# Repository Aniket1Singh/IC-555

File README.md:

# IC-555
PCB design of IC-555 timer working in Astable Mode.

This repository contains the design files for a PCB based on the IC-555 timer in astable mode. The design was created using KiCad, and all the necessary files are included here.

What’s Included

KiCad project files

Gerber files for PCB fabrication

Schematic and board design

How to Use

Open the KiCad project files to view or modify the design.

Use the Gerber files to manufacture the PCB.

Assemble the circuit by soldering the required components.

Applications-
LED blinking circuits,
Square wave generators,
Simple tone generators,
Learning about the IC-555 timer.
Feel free to use or modify this design for your projects! 😊

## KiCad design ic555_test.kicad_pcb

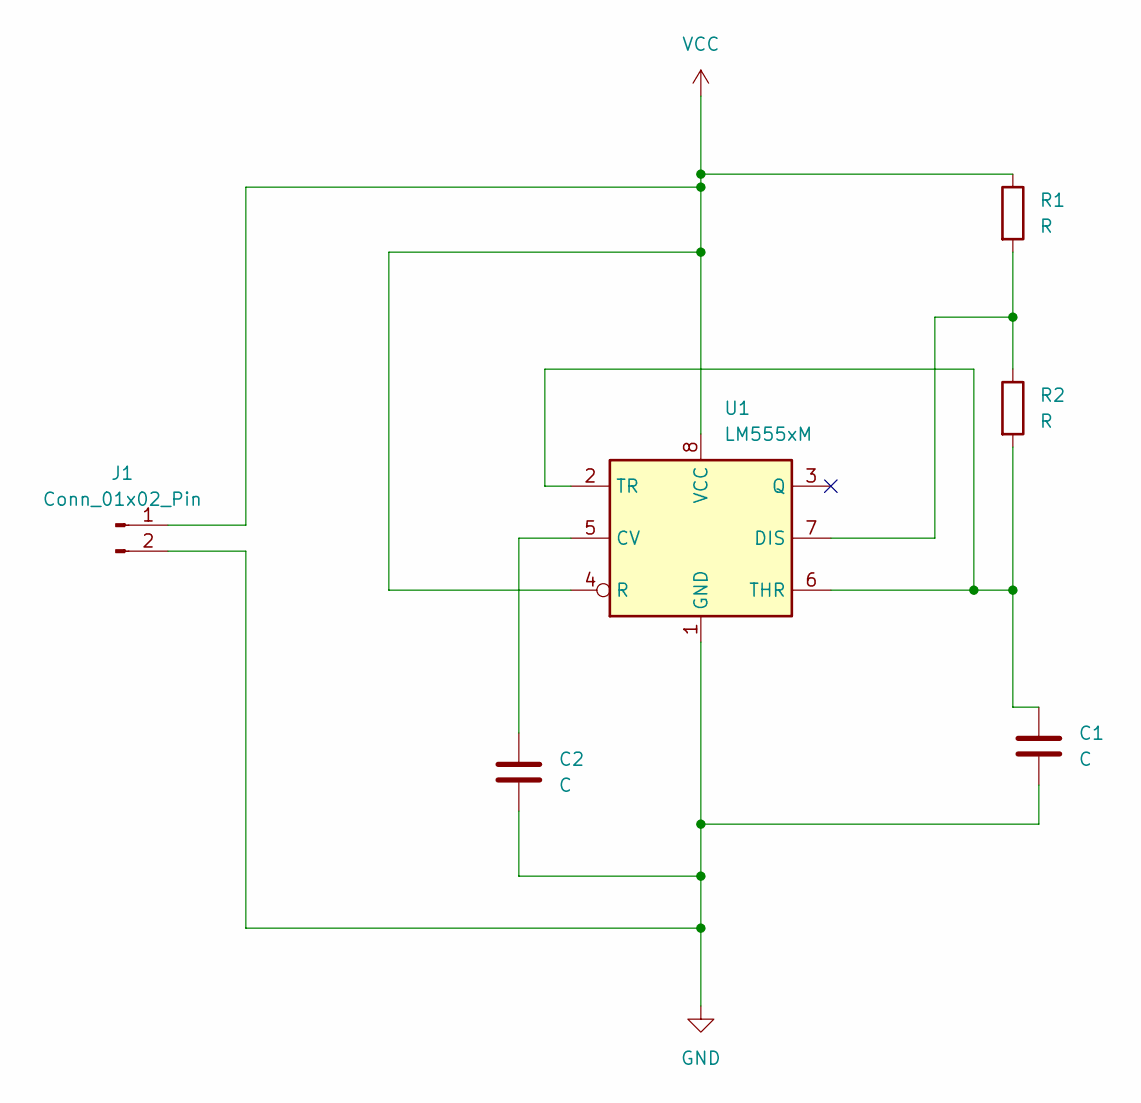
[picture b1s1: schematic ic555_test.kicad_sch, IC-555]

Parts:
C1, C2: C; CP_Axial_L10.0mm_D4.5mm_P15.00mm_Horizontal
J1: Conn_01x02_Pin; TE_440054-2_1x02_P2.00mm_Vertical
R1, R2: R; R_Axial_DIN0204_L3.6mm_D1.6mm_P1.90mm_Vertical
U1: LM555xM; SOIC-8_3.9x4.9mm_P1.27mm

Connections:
GND: C1.2, C2.2, J1.2, U1.1 (GND)
unnamed: C2.1, U1.5 (CV)
unnamed: R1.2, R2.1, U1.7 (DIS)
unnamed: C1.1, R2.2, U1.2 (TR), U1.6 (THR)
VCC: J1.1, R1.1, U1.4 (R), U1.8 (VCC)

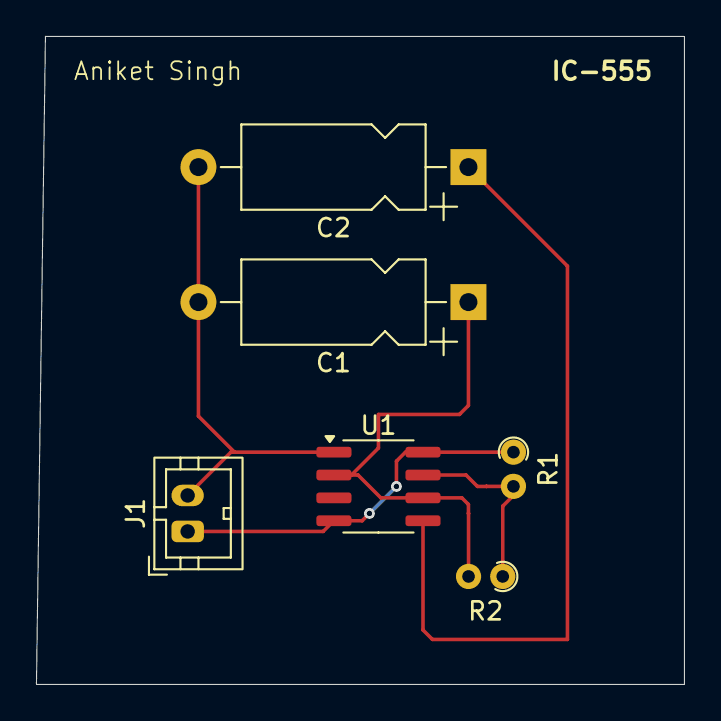
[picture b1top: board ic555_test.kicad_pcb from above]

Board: 2 copper layers, 36.0 x 36.0 mm, 6 parts (0 on the bottom side), 5 nets.
